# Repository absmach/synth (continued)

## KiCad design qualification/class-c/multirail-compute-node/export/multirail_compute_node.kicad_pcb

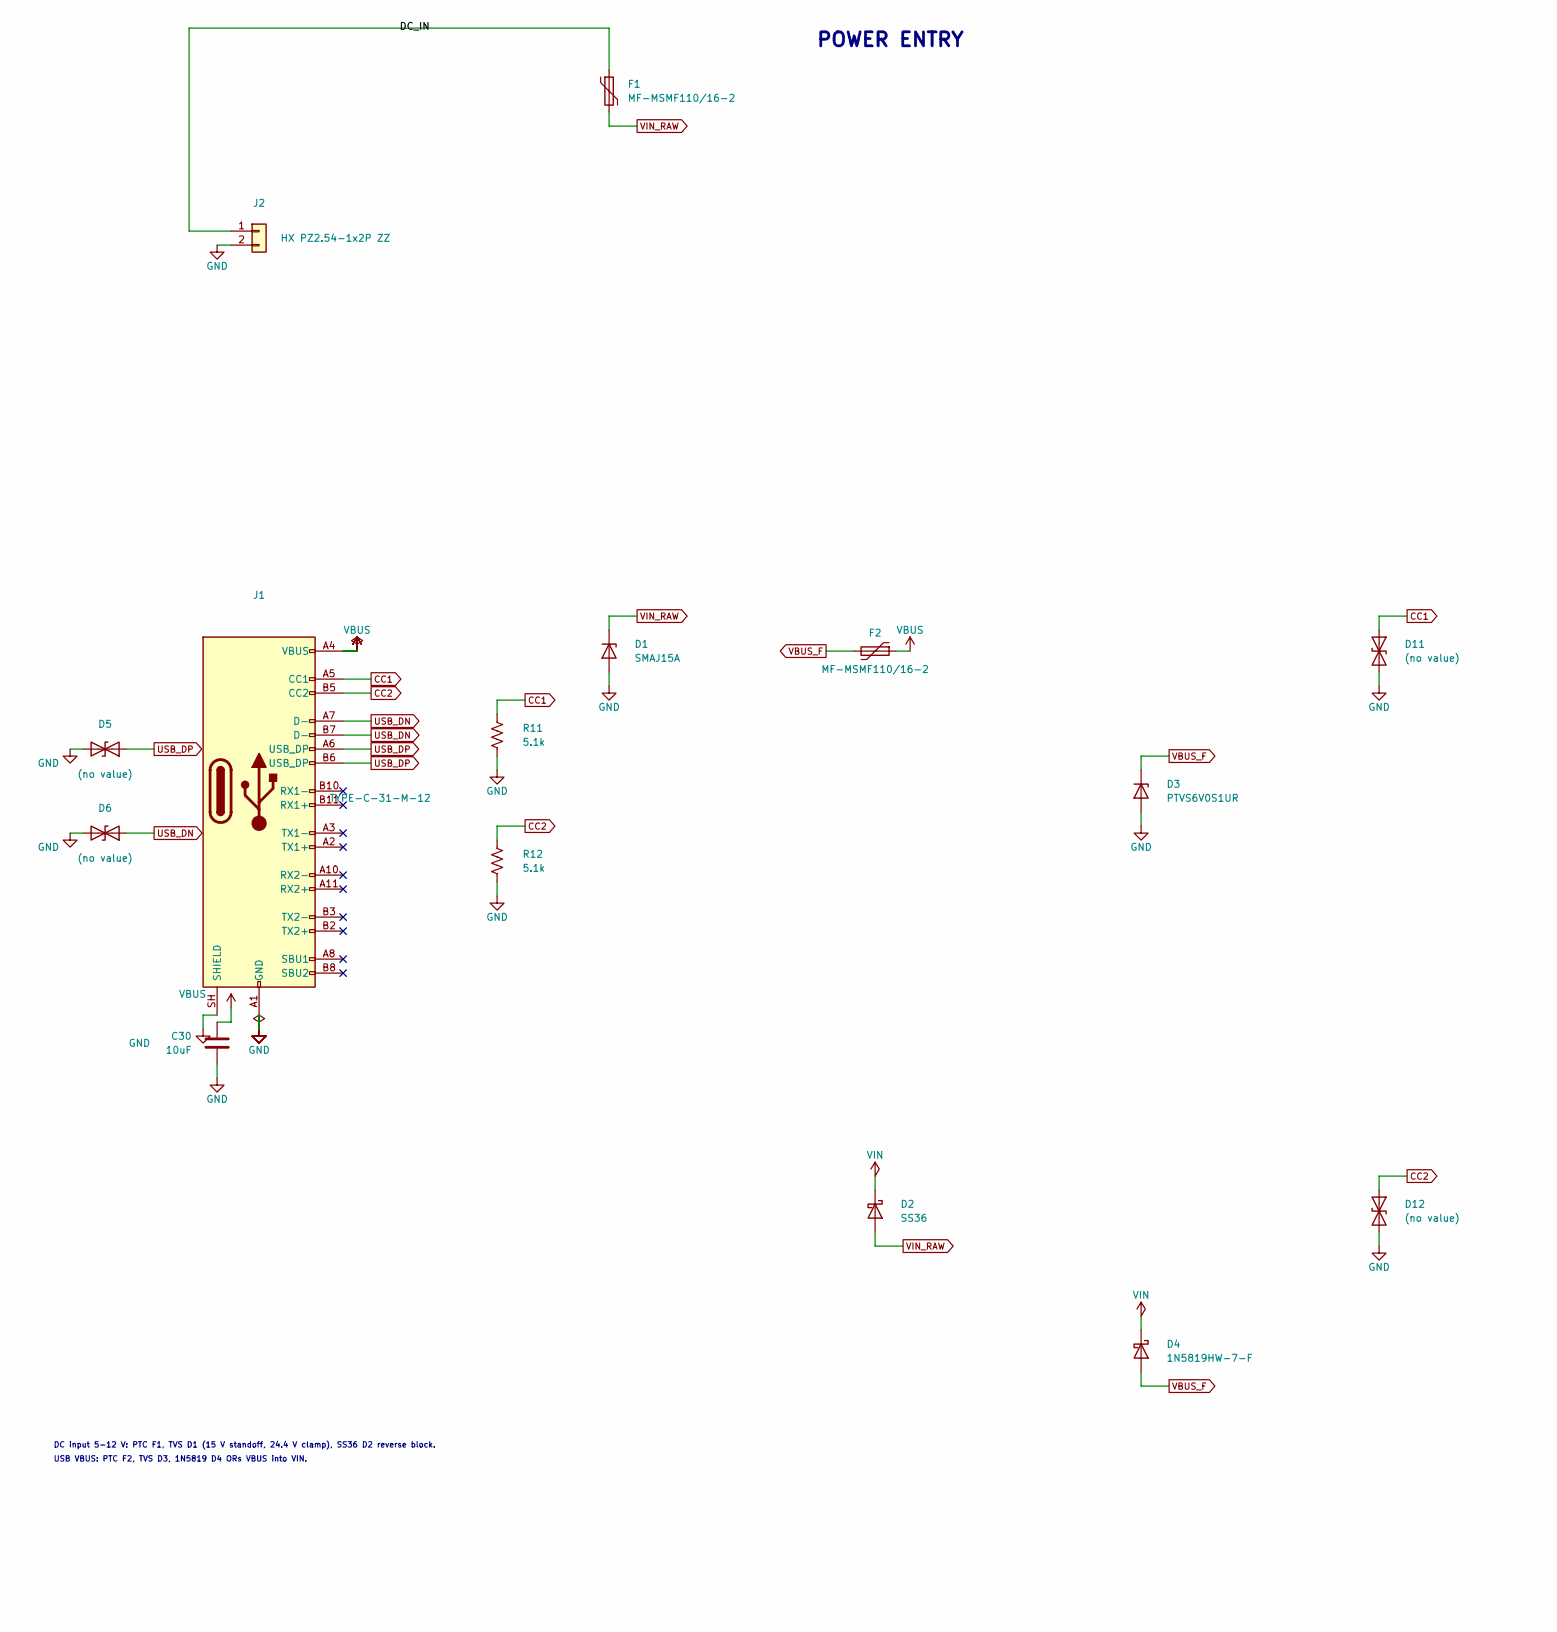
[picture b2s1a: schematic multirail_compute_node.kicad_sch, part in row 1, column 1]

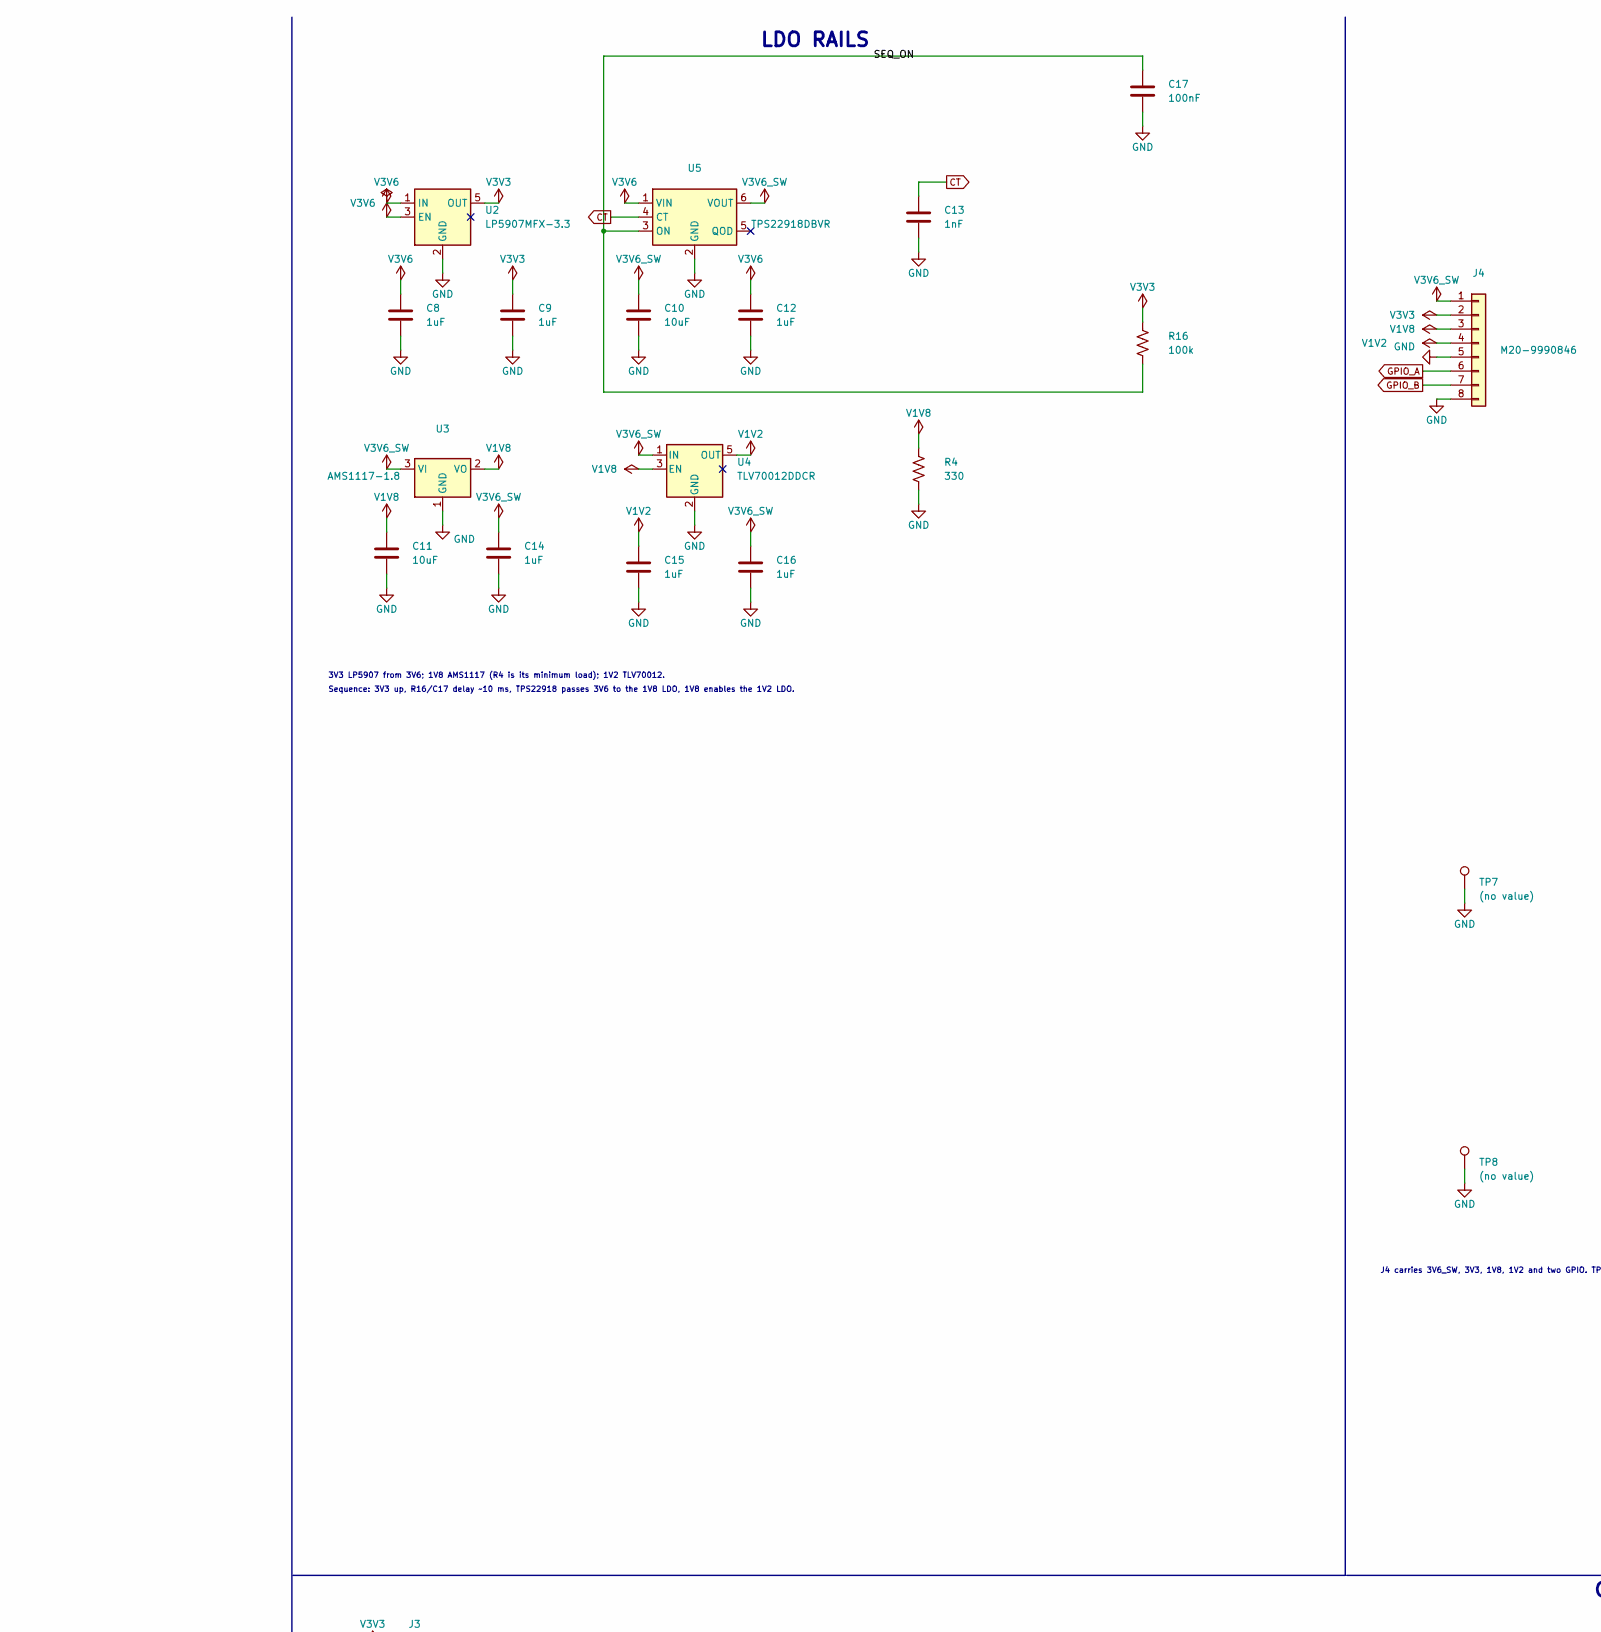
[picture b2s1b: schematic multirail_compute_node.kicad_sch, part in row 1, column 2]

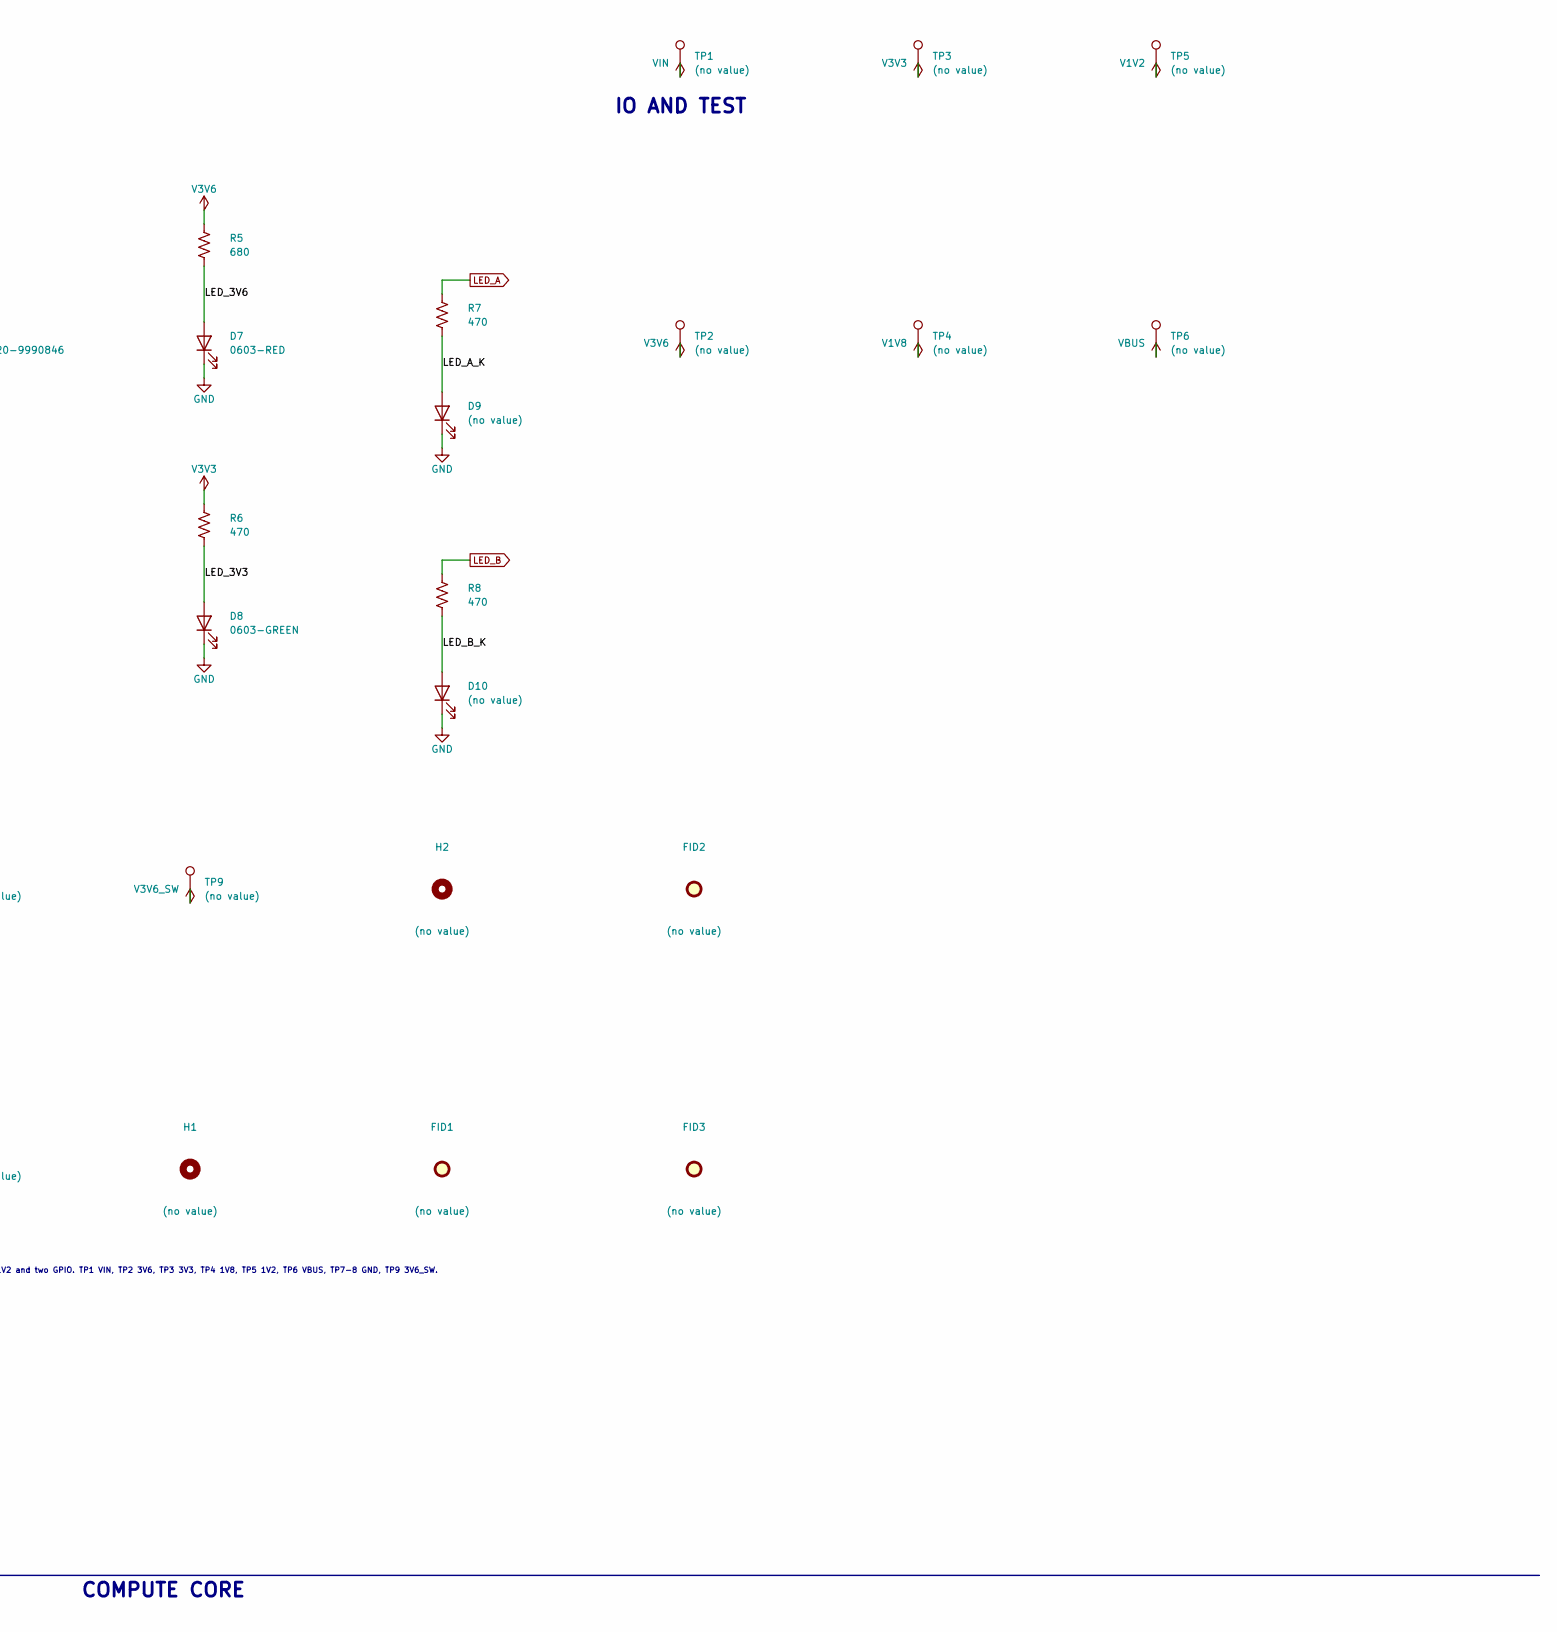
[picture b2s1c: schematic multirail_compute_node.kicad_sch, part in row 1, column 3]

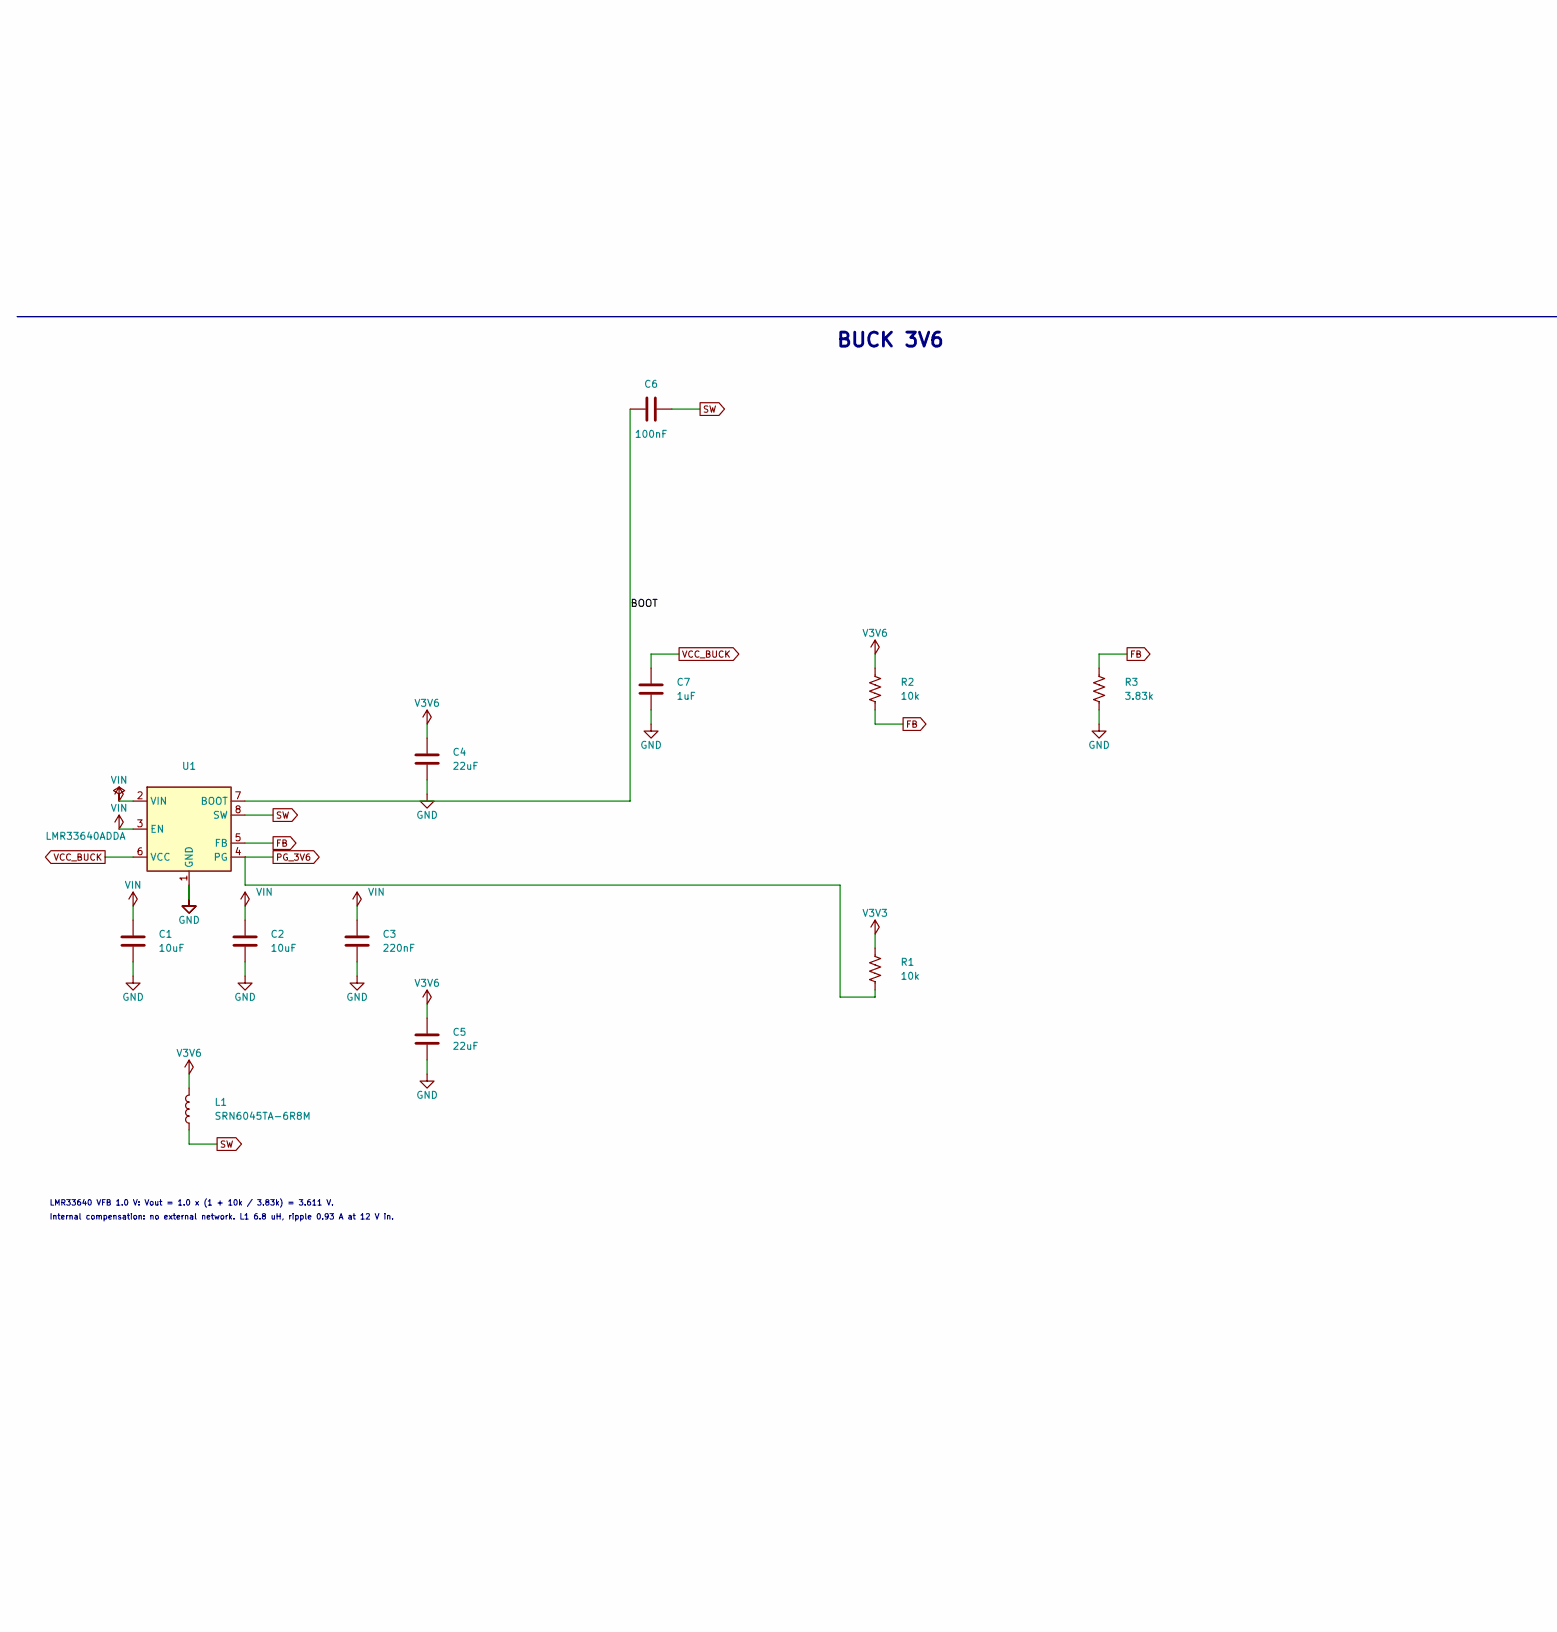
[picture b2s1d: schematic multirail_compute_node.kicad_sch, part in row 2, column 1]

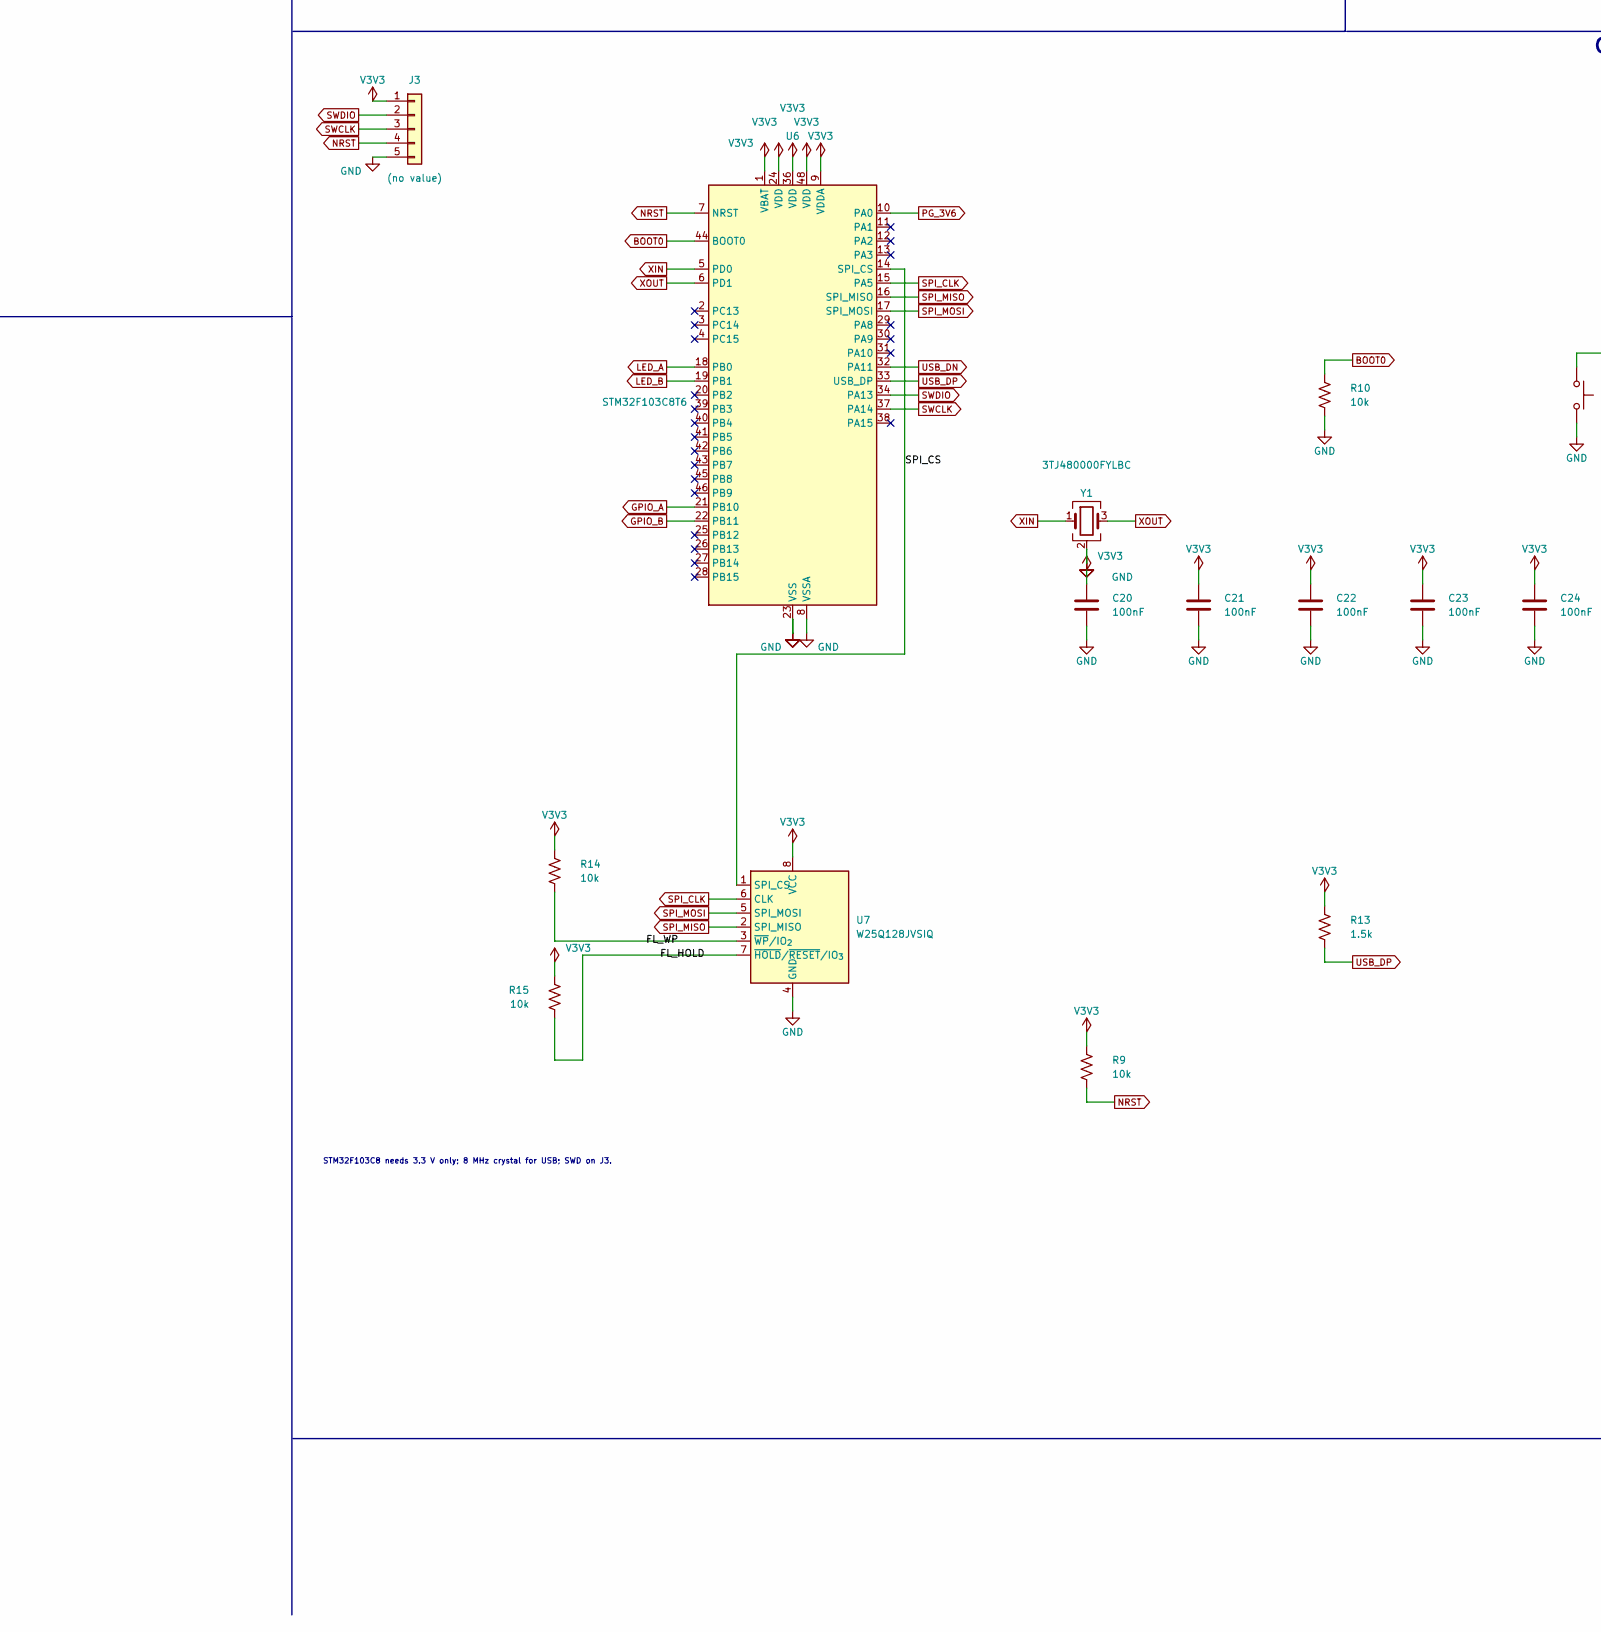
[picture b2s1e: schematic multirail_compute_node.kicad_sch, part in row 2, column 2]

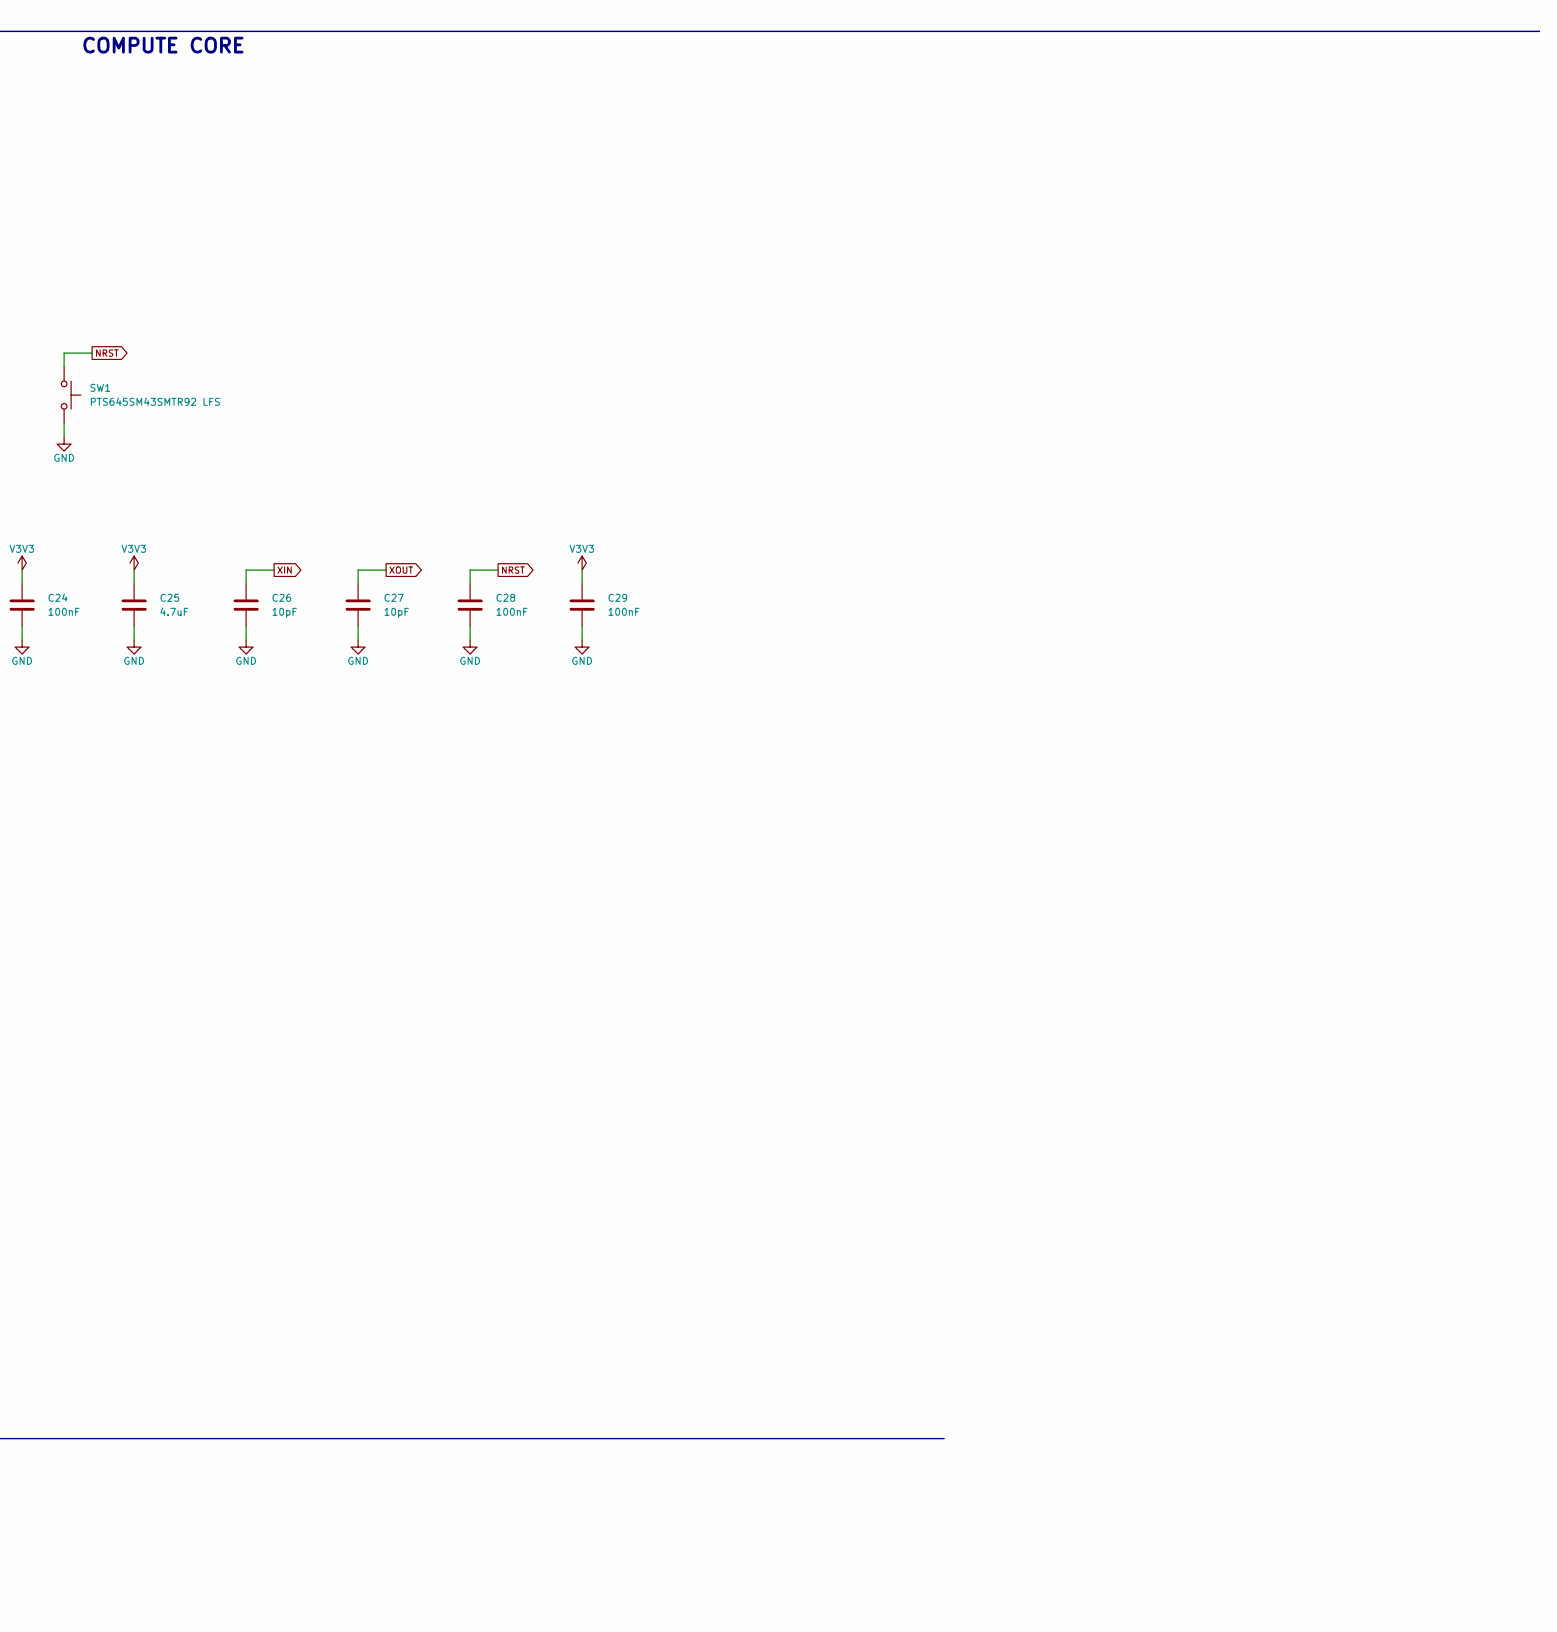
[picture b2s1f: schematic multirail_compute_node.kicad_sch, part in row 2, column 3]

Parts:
C1, C2: 10uF; C_1206_3216Metric
C3: 220nF; C_0603_1608Metric
C4, C5: 22uF; C_0805_2012Metric
C6, C17, C20, C21, C22, C23, C24, C28, C29: 100nF; C_0603_1608Metric
C7, C8, C9, C12, C14, C15, C16: 1uF; C_0603_1608Metric
C10, C11, C30: 10uF; C_0805_2012Metric
C13: 1nF; C_0603_1608Metric
C25: 4.7uF; C_0805_2012Metric
C26, C27: 10pF; C_0603_1608Metric
D1: SMAJ15A; D_SMA; MPN SMAJ15A
D2: SS36; D_SMC; MPN SS36
D3: PTVS6V0S1UR; Nexperia_CFP3_SOD-123W; MPN PTVS6V0S1UR
D4: 1N5819HW-7-F; D_SOD-123; MPN 1N5819HW-7-F; LCSC C82544
D5, D6, D11, D12: (no value); D_SOD-323
D7: 0603-RED; LED_0603_1608Metric; MPN 0603-RED; LCSC C2286
D8: 0603-GREEN; LED_0603_1608Metric; MPN 0603-GREEN; LCSC C72043
D9, D10: (no value); LED_0603_1608Metric
F1, F2: MF-MSMF110/16-2; Fuse_1812_4532Metric; MPN MF-MSMF110/16-2; LCSC C210834
FID1, FID2, FID3: (no value); Fiducial_1mm_Mask2mm
H1, H2: (no value); MountingHole_2.5mm
J1: TYPE-C-31-M-12; USB_C_Receptacle_HRO_TYPE-C-31-M-12; MPN TYPE-C-31-M-12; LCSC C165948
J2: HX PZ2.54-1x2P ZZ; PinHeader_1x02_P2.54mm_Vertical; MPN HX PZ2.54-1x2P ZZ; LCSC C32713268
J3: (no value); PinHeader_1x05_P2.54mm_Vertical
J4: M20-9990846; PinHeader_1x08_P2.54mm_Vertical; MPN M20-9990846
L1: SRN6045TA-6R8M; L_Bourns_SRN6045TA; MPN SRN6045TA-6R8M
R1, R2, R9, R10, R14, R15: 10k; R_0603_1608Metric
R3: 3.83k; R_0603_1608Metric
R4: 330; R_0603_1608Metric
R5: 680; R_0603_1608Metric
R6, R7, R8: 470; R_0603_1608Metric
R11, R12: 5.1k; R_0603_1608Metric
R13: 1.5k; R_0603_1608Metric
R16: 100k; R_0603_1608Metric
SW1: PTS645SM43SMTR92 LFS; SW_SPST_PTS645Sx43SMTR92; MPN PTS645SM43SMTR92 LFS; LCSC C221880
TP1, TP2, TP3, TP4, TP5, TP6, TP7, TP8, TP9: (no value); TestPoint_Pad_D1.5mm
U1: LMR33640ADDA; HSOP-8-1EP_3.9x4.9mm_P1.27mm_EP2.41x3.1mm; MPN LMR33640ADDA
U2: LP5907MFX-3.3; SOT-23-5; MPN LP5907MFX-3.3; LCSC C83437
U3: AMS1117-1.8; SOT-223-3_TabPin2; MPN AMS1117-1.8; LCSC C6188
U4: TLV70012DDCR; TSOT-23-5; MPN TLV70012DDCR
U5: TPS22918DBVR; SOT-23-6; MPN TPS22918DBVR; LCSC C131941
U6: STM32F103C8T6; LQFP-48_7x7mm_P0.5mm; MPN STM32F103C8T6; LCSC C8734
U7: W25Q128JVSIQ; SOIC-8_5.3x5.3mm_P1.27mm; MPN W25Q128JVSIQ; LCSC C97521
Y1: 3TJ480000FYLBC; Crystal_SMD_3225-4Pin_3.2x2.5mm; MPN 3TJ480000FYLBC

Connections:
BOOT: C6.1, U1.7 (BOOT)
BOOT0: R10.1, U6.44 (BOOT0)
CC1: D11.1 (A1), J1.A5 (CC1), R11.1
CC2: D12.1 (A1), J1.B5 (CC2), R12.1
CT: C13.1, U5.4 (CT)
DC_IN: F1.1, J2.1
FB: R2.2, R3.1, U1.5 (FB)
FL_HOLD: R15.1, U7.7 (~HOLD/~RESET/IO_{3})
FL_WP: R14.1, U7.3 (~WP/IO_{2})
GND: C1.2, C2.2, C3.2, C4.2, C5.2, C7.2, C8.2, C9.2, C10.2, C11.2, C12.2, C13.2, C14.2, C15.2, C16.2, C17.2, C20.2, C21.2, C22.2, C23.2, C24.2, C25.2, C26.2, C27.2, C28.2, C29.2, C30.2, D1.2 (A), D3.2 (A), D5.2 (A2), D6.2 (A2), D7.1 (K), D8.1 (K), D9.1 (K), D10.1 (K), D11.2 (A2), D12.2 (A2), J1.A1 (GND), J1.A12 (GND), J1.B1 (GND), J1.B12 (GND), J1.SH (SHIELD), J2.2, J3.5, J4.5, J4.8, R3.2, R4.2, R10.2, R11.2, R12.2, SW1.2, TP7.1, TP8.1, U1.1 (GND), U1.9 (GND), U2.2 (GND), U3.1 (GND), U4.2 (GND), U5.2 (GND), U6.8 (VSSA), U6.23 (VSS), U6.35 (VSS), U6.47 (VSS), U7.4 (GND), Y1.2 (G), Y1.4 (G)
GPIO_A: J4.6, U6.21 (PB10)
GPIO_B: J4.7, U6.22 (PB11)
LED_3V3: D8.2 (A), R6.2
LED_3V6: D7.2 (A), R5.2
LED_A: R7.1, U6.18 (PB0)
LED_A_K: D9.2 (A), R7.2
LED_B: R8.1, U6.19 (PB1)
LED_B_K: D10.2 (A), R8.2
NRST: C28.1, J3.4, R9.2, SW1.1, U6.7 (NRST)
PG_3V6: R1.1, U1.4 (PG), U6.10 (PA0)
SEQ_ON: C17.1, R16.2, U5.3 (ON)
SPI_CLK: U6.15 (PA5), U7.6 (CLK)
SPI_CS: U6.14 (PA4), U7.1 (~CS)
SPI_MISO: U6.16 (PA6), U7.2 (DO/IO_{1})
SPI_MOSI: U6.17 (PA7), U7.5 (DI/IO_{0})
SW: C6.2, L1.1, U1.8 (SW)
SWCLK: J3.3, U6.37 (PA14)
SWDIO: J3.2, U6.34 (PA13)
USB_DN: D6.1 (A1), J1.A7 (D-), J1.B7 (D-), U6.32 (PA11)
USB_DP: D5.1 (A1), J1.A6 (D+), J1.B6 (D+), R13.2, U6.33 (PA12)
V1V2: C15.1, J4.4, TP5.1, U4.5 (OUT)
V1V8: C11.1, J4.3, R4.1, TP4.1, U3.2 (VO), U4.3 (EN)
V3V3: C9.1, C20.1, C21.1, C22.1, C23.1, C24.1, C25.1, C29.1, J3.1, J4.2, R1.2, R6.1, R9.1, R13.1, R14.2, R15.2, R16.1, TP3.1, U2.5 (OUT), U6.1 (VBAT), U6.9 (VDDA), U6.24 (VDD), U6.36 (VDD), U6.48 (VDD), U7.8 (VCC)
V3V6: C4.1, C5.1, C8.1, C12.1, L1.2, R2.1, R5.1, TP2.1, U2.1 (IN), U2.3 (EN), U5.1 (VIN)
V3V6_SW: C10.1, C14.1, C16.1, J4.1, TP9.1, U3.3 (VI), U4.1 (IN), U5.6 (VOUT)
VBUS: C30.1, F2.1, J1.A4 (VBUS), J1.A9 (VBUS), J1.B4 (VBUS), J1.B9 (VBUS), TP6.1
VBUS_F: D3.1 (K), D4.2 (A), F2.2
VCC_BUCK: C7.1, U1.6 (VCC)
VIN: C1.1, C2.1, C3.1, D2.1 (K), D4.1 (K), TP1.1, U1.2 (VIN), U1.3 (EN)
VIN_RAW: D1.1 (K), D2.2 (A), F1.2
XIN: C26.1, U6.5 (PD0), Y1.1
XOUT: C27.1, U6.6 (PD1), Y1.3

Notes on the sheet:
POWER ENTRY
BUCK 3V6
LDO RAILS
COMPUTE CORE
IO AND TEST
DC input 5-12 V: PTC F1, TVS D1 (15 V standoff, 24.4 V clamp), SS36 D2 reverse block.
USB VBUS: PTC F2, TVS D3, 1N5819 D4 ORs VBUS into VIN.
LMR33640 VFB 1.0 V: Vout = 1.0 x (1 + 10k / 3.83k) = 3.611 V.
Internal compensation: no external network. L1 6.8 uH, ripple 0.93 A at 12 V in.
3V3 LP5907 from 3V6; 1V8 AMS1117 (R4 is its minimum load); 1V2 TLV70012.
Sequence: 3V3 up, R16/C17 delay ~10 ms, TPS22918 passes 3V6 to the 1V8 LDO, 1V8 enables the 1V2 LDO.
STM32F103C8 needs 3.3 V only; 8 MHz crystal for USB; SWD on J3.
J4 carries 3V6_SW, 3V3, 1V8, 1V2 and two GPIO. TP1 VIN, TP2 3V6, TP3 3V3, TP4 1V8, TP5 1V2, TP6 VBUS, TP7-8 GND, TP9 3V6_SW.
